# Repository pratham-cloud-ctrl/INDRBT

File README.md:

# INDRBT · Six-axis robot arm and parallel gripper

An original digital robotics project connecting mechanical design, robot mathematics, motion, feedback control and a routed KiCad interface board.

**[OPEN THE INTERACTIVE ENGINEERING SHOWCASE](https://pratham-cloud-ctrl.github.io/INDRBT/)** — inspect the 3D robot, 3D PCB, components, schematics and theory in your browser. No CAD application or GitHub sign-in is needed.

**[DOWNLOAD THE PUBLIC ENGINEERING PACKS](https://github.com/pratham-cloud-ctrl/INDRBT/releases/tag/indrbt-2026-10-28)** — STEP/STL CAD, native FreeCAD, the KiCad project, PCB STEP and a combined offline viewer/CAD pack. The repository and release are public; no private access is required. [Choose a format and open it](06_Complete_Project_Source/docs/cad_downloads.md). The published GitHub Pages showcase includes the browser viewers and download controls.

**[CAD & mechanical design](01_CAD_Models/README.md) · [Electronics & KiCad](04_Electronics/README.md) · [Theory & calculations](03_Reports_and_Results/README.md)**

**6 revolute joints · 54 CAD components · 790 mm nominal reach · 90 mm jaw opening**

Digital engineering model · v1.2.0 · DIGITAL SCOPE COMPLETE

## Explore the project on GitHub

You can inspect the design, drawings, circuit and calculations here without installing engineering software. Each tour starts with actual project images, then links to the native files and supporting evidence.

| Explore | Illustrated tour | Inspect the details |
|---|---|---|
| **Mechanical design** | [Arm, joints, tool interface and gripper](06_Complete_Project_Source/docs/cad_tour.md) | [Dimensioned drawings](01_CAD_Models/Drawings/engineering_interfaces.pdf) · [54-part catalog](06_Complete_Project_Source/docs/component_catalog.md) · [FreeCAD / STEP / STL](01_CAD_Models/README.md#download-and-edit) |
| **Electronics & KiCad** | [Follow power and signals through the board](06_Complete_Project_Source/docs/electronics_tour.md) | [Schematic PDF](04_Electronics/exports/joint_interface.pdf) · [PCB layers](04_Electronics/exports/pcb_layers.pdf) · [BOM](04_Electronics/bom.csv) · [Native KiCad project](04_Electronics/README.md#open-the-kicad-project) |
| **Theory & simulation** | [From geometry to a working digital task](06_Complete_Project_Source/docs/engineering_walkthrough.md) | [Equation guide](06_Complete_Project_Source/docs/theory_guide.md) · [Chapters and results](06_Complete_Project_Source/docs/README.md) · [Engineering report](06_Complete_Project_Source/docs/engineering_report.md) |

[Project purpose and original goals](06_Complete_Project_Source/docs/project_alignment.md) · [Complete documentation index](06_Complete_Project_Source/docs/README.md) · [Requirements and evidence](06_Complete_Project_Source/docs/validation_matrix.md)

## Watch the task, then inspect the design

The 9.24 s demonstration approaches, grasps, transfers and releases an object. The browser viewer animates the actual CAD meshes and can isolate every part. The GIF above is a forward-kinematics line view; object attachment is idealized in the simulation.

**Inspect online:** [move and isolate the robot](https://pratham-cloud-ctrl.github.io/INDRBT/#robot), [search the PCB and highlight nets](https://pratham-cloud-ctrl.github.io/INDRBT/#pcb), or [rotate the native 3D board](https://pratham-cloud-ctrl.github.io/INDRBT/#pcb3d). GitHub can decline previews of CAD files; the public showcase serves the actual display assets directly.

**For optional offline use:** [download the current repository](https://github.com/pratham-cloud-ctrl/INDRBT/archive/refs/heads/main.zip), extract it and open **OPEN_3D_VIEWER.cmd** on Windows. On any system, open `02_Simulation_and_Animation/Interactive_3D_Viewer.html` in a browser. It provides a local copy of the joint controls, part isolation and playback available online. GitHub shows this HTML source rather than executing it.

| Gripper and interchangeable tool interface | Routed joint / sensor interface |
|---|---|
|  |  |
| [Explore the mechanical design](06_Complete_Project_Source/docs/cad_tour.md) | [Explore the circuit and PCB](06_Complete_Project_Source/docs/electronics_tour.md) |

## Follow the engineering argument

The [engineering walkthrough](06_Complete_Project_Source/docs/engineering_walkthrough.md) follows one question: can the chosen geometry move a tool through a useful task, carry the assumed load in the analytical model, and track its commanded motion?

1. **Geometry → tool pose:** [Coordinate frames, FK, IK and the Jacobian](06_Complete_Project_Source/docs/02_kinematics.md).
2. **Pose → useful motion:** [Recorded task and motion limits](02_Simulation_and_Animation/README.md).
3. **Load → mechanical decisions:** [Gravity torque, drive sizing, stiffness and gripper calculations](06_Complete_Project_Source/docs/03_mechanical_analysis.md).
4. **Command → feedback:** [PID model and actual simulation curves](06_Complete_Project_Source/docs/theory_guide.md#8-understand-the-controller-experiment).
5. **Signals → interface hardware:** [Encoder, limit, external-drive and RS-485 circuit](06_Complete_Project_Source/docs/electronics_tour.md).

## What is verified

The [executed validation](06_Complete_Project_Source/results/validation/validation_report.md) records **91 tests with zero failures or errors**, native CAD inspection, sampled clearance, numerical checks and native KiCad ERC/DRC/connectivity checks. The [requirements matrix](06_Complete_Project_Source/docs/validation_matrix.md) maps each claim to its evidence; the [project journal](06_Complete_Project_Source/docs/project_journal.md) records actual faults and corrections.

Payload **4 kg** and repeatability **±0.1 mm** are targets. The project is entirely digital: analytical structure, simplified independent-axis control and sampled collision checks do not establish physical performance, manufacturing qualification, EMC or functional safety. The [scope audit](06_Complete_Project_Source/docs/digital_scope_audit.md) explains these boundaries.

## Find files or reproduce the work

| Folder | Start here |
|---|---|
| [01 · CAD models](01_CAD_Models/README.md) | Visual mechanical guide, native FreeCAD/Blender, six STEP/STL assemblies and 54 parts |
| [02 · Simulation and animation](02_Simulation_and_Animation/README.md) | Offline 3D viewer, recorded motion, workspace and PID plots |
| [03 · Theory, reports and results](03_Reports_and_Results/README.md) | Reading route, equations, calculations, experiments and verification |
| [04 · Electronics and KiCad](04_Electronics/README.md) | Schematic, board previews, native project, components and fabrication exports |
| [05 · Reference and project notes](05_Reference_and_Project_Notes/README.md) | Requirements, architecture, decisions and development journal |
| [06 · Complete source](06_Complete_Project_Source/README.md) | Installation, reproduction commands, scripts, tests and authoritative configuration |

After downloading, **OPEN_PROJECT_HOME.cmd** opens the local guide; **OPEN_FREECAD_MODEL.cmd** opens the solid assembly; **OPEN_PCB_LAYOUT.cmd** opens the board. Native CAD/KiCad files require their applications. PDF, PNG, SVG, CSV and Markdown provide immediate previews on GitHub.

The complete source is authoritative; numbered presentation folders contain verified copies. The [reproduction guide](06_Complete_Project_Source/README.md#run) and [contribution guide](CONTRIBUTING.md) explain regeneration. The last packaged engineering release is [v1.2.0](https://github.com/pratham-cloud-ctrl/INDRBT/releases/tag/indrbt-2026-10-28); the current repository includes the latest reading guides.

MIT-licensed original source · [License](LICENSE) · [Citation](CITATION.cff) · [Software checks](https://github.com/pratham-cloud-ctrl/INDRBT/actions/workflows/validation.yml)

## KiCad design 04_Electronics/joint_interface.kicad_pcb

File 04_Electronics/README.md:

# Electronics & KiCad · Joint / sensor interface

[← Project home](../README.md) · [CAD](../01_CAD_Models/README.md) · [Theory](../03_Reports_and_Results/README.md)

**[Inspect the interactive PCB](https://pratham-cloud-ctrl.github.io/INDRBT/#pcb) · [Rotate the 3D board](https://pratham-cloud-ctrl.github.io/INDRBT/#pcb3d) · [Zoom the schematic](https://pratham-cloud-ctrl.github.io/INDRBT/#schematic)**

Search components, cross-highlight the BOM, follow connected nets and inspect the actual board without installing KiCad.

**Start with the [illustrated circuit and PCB tour](../06_Complete_Project_Source/docs/electronics_tour.md).** Follow the regulated supply, encoder/limit inputs, external-drive commands and RS-485 interface, then match each block to the schematic and board.

**100 × 100 mm · Four copper layers · 44 schematic components · 48 PCB footprints including four mounting holes**

## Browse without KiCad

| Inspect | Open on GitHub |
|---|---|
| Circuit connections and values | [Schematic PDF](exports/joint_interface.pdf) · [Zoomable schematic SVG](exports/joint_interface.svg) |
| Board layout and references | [Top view](exports/pcb_top.png) · [Top copper SVG](exports/pcb_top.svg) · [Six-page layer PDF](exports/pcb_layers.pdf) |
| Ground, power and bottom routing | [Ground plane](exports/pcb_ground_plane.svg) · [Power plane](exports/pcb_power_plane.svg) · [Bottom copper](exports/pcb_bottom.svg) |
| Components and selection reasoning | [Component guide](../06_Complete_Project_Source/docs/electronics_components.md) · [BOM table](bom.csv) |
| Supply budget, filters and interface limits | [Electrical design chapter](../06_Complete_Project_Source/docs/05_electronics.md) · [Calculated values](interface_calculations.json) |
| Actual design-rule and connectivity evidence | [ERC](erc_report.json) · [DRC](pcb_drc_report.json) · [PCB verification](pcb_verification.json) |

References such as **U1**, **R5** or **J3** identify the same part in the schematic, layout and BOM. The tour explains the reference groups and **DNP** population choices.

## Open the KiCad project

**[Public KiCad and PCB STEP downloads](https://github.com/pratham-cloud-ctrl/INDRBT/releases/tag/indrbt-2026-10-28)** — the editable project with schematic, board and custom library context, plus board geometry for mechanical CAD. Follow the [opening guide](../06_Complete_Project_Source/docs/cad_downloads.md#open-the-kicad-project). GitHub downloads are public. The published GitHub Pages showcase includes the browser viewers and download controls.

1. For optional offline editing, download and extract the **complete repository**, keeping this folder together.
2. Open [joint_interface.kicad_pro](joint_interface.kicad_pro) in **KiCad 10**, then choose the schematic or PCB editor.
3. On Windows, **OPEN_PCB_LAYOUT.cmd** in the parent folder opens the routed board directly.

| Native item | File |
|---|---|
| KiCad project | [joint_interface.kicad_pro](joint_interface.kicad_pro) |
| Schematic | [joint_interface.kicad_sch](joint_interface.kicad_sch) |
| Routed PCB | [joint_interface.kicad_pcb](joint_interface.kicad_pcb) |
| Project-local library table | [fp-lib-table](fp-lib-table) |
| Manufacturer-specific fuse land pattern | [INDRBT_Interface.pretty](INDRBT_Interface.pretty) |

Keep the library table and local footprint folder beside the project. F1 uses a Bourns MF-NSMF025X-2 land pattern stored here; downloading only the PCB omits part of the editable project. The 3D render shows F1's lands because a dedicated fuse body model is not supplied.

## Fabrication and source

[Fabrication ZIP](fabrication/joint_interface_fabrication.zip) · [Gerbers, drills and positions](fabrication) · [Assembly drawing](exports/pcb_assembly.svg) · [Source and verification commands](../06_Complete_Project_Source/electronics/README.md)

This is a digital low-voltage interface for an external controller and drive. The board has no MCU or motor power stage. The E-stop connection monitors an auxiliary contact; it does not implement torque interruption. Native checks and fabrication exports are review evidence, with physical thermal, EMC and manufacturing qualification outside the project scope.

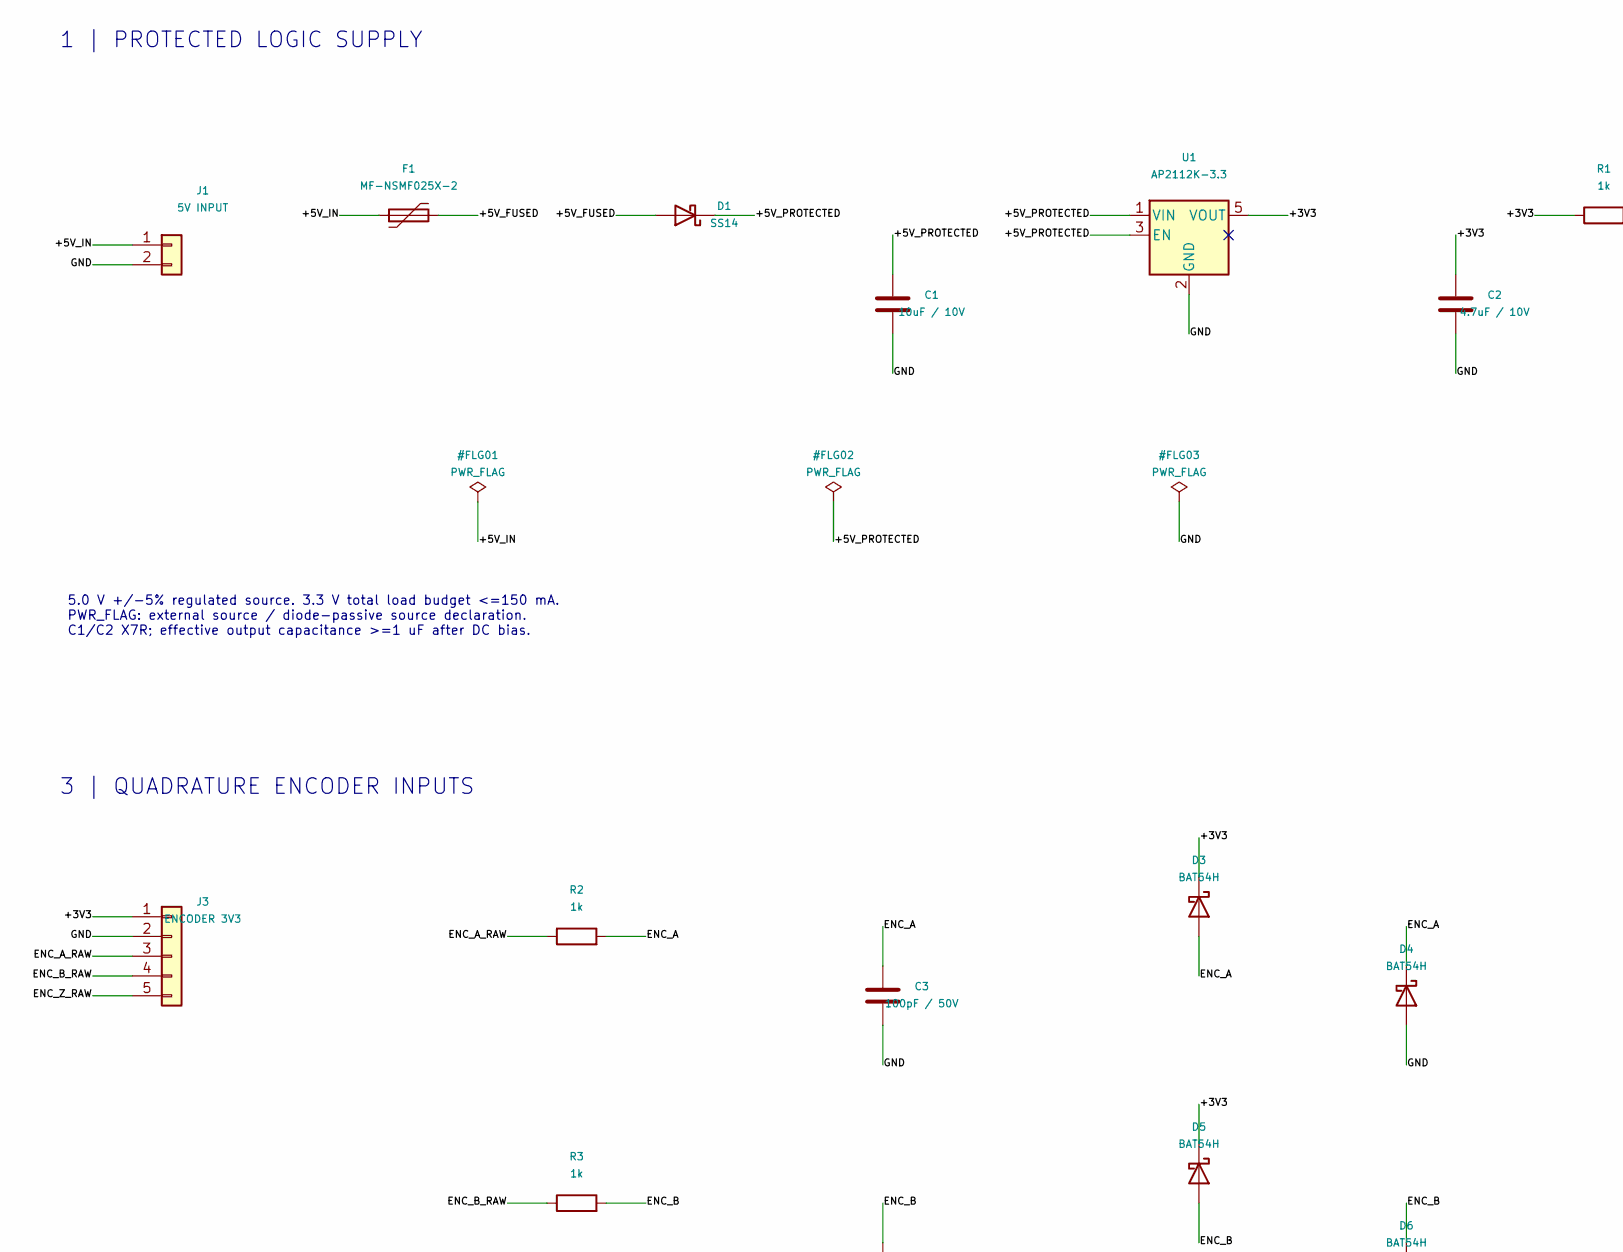
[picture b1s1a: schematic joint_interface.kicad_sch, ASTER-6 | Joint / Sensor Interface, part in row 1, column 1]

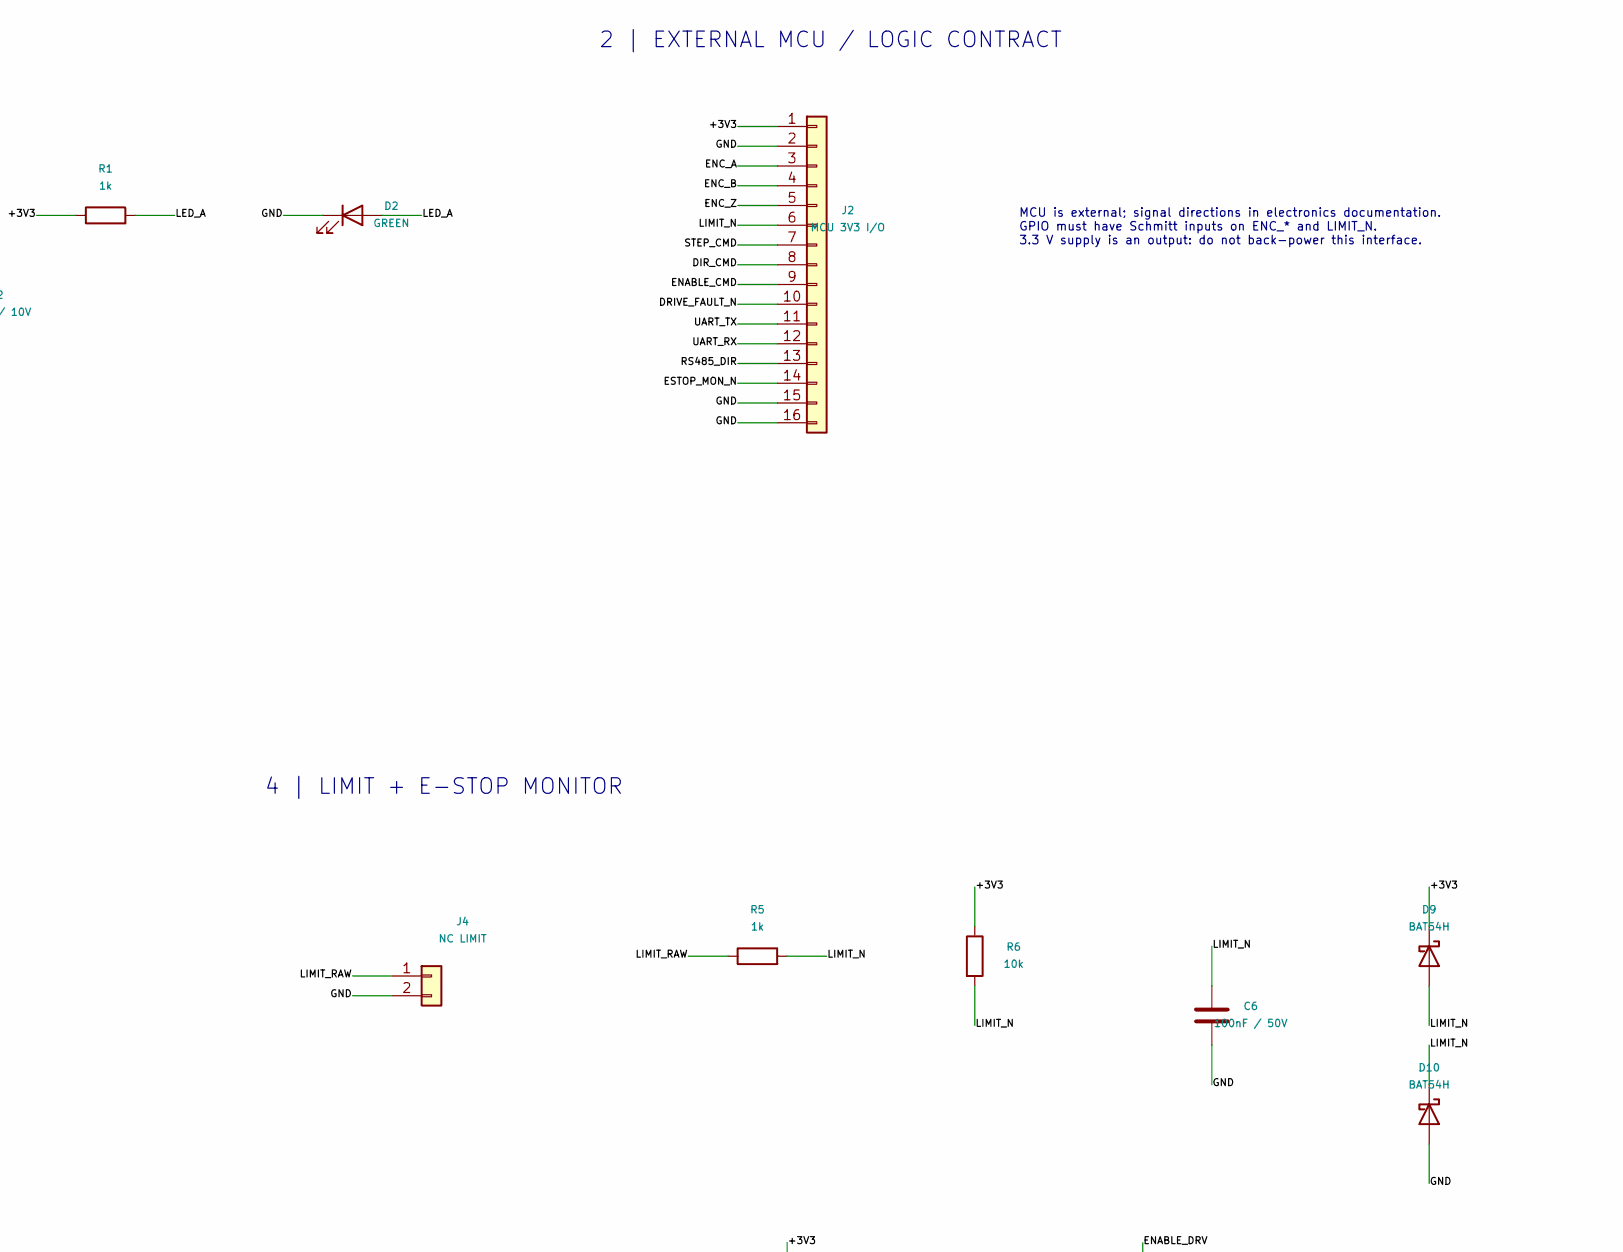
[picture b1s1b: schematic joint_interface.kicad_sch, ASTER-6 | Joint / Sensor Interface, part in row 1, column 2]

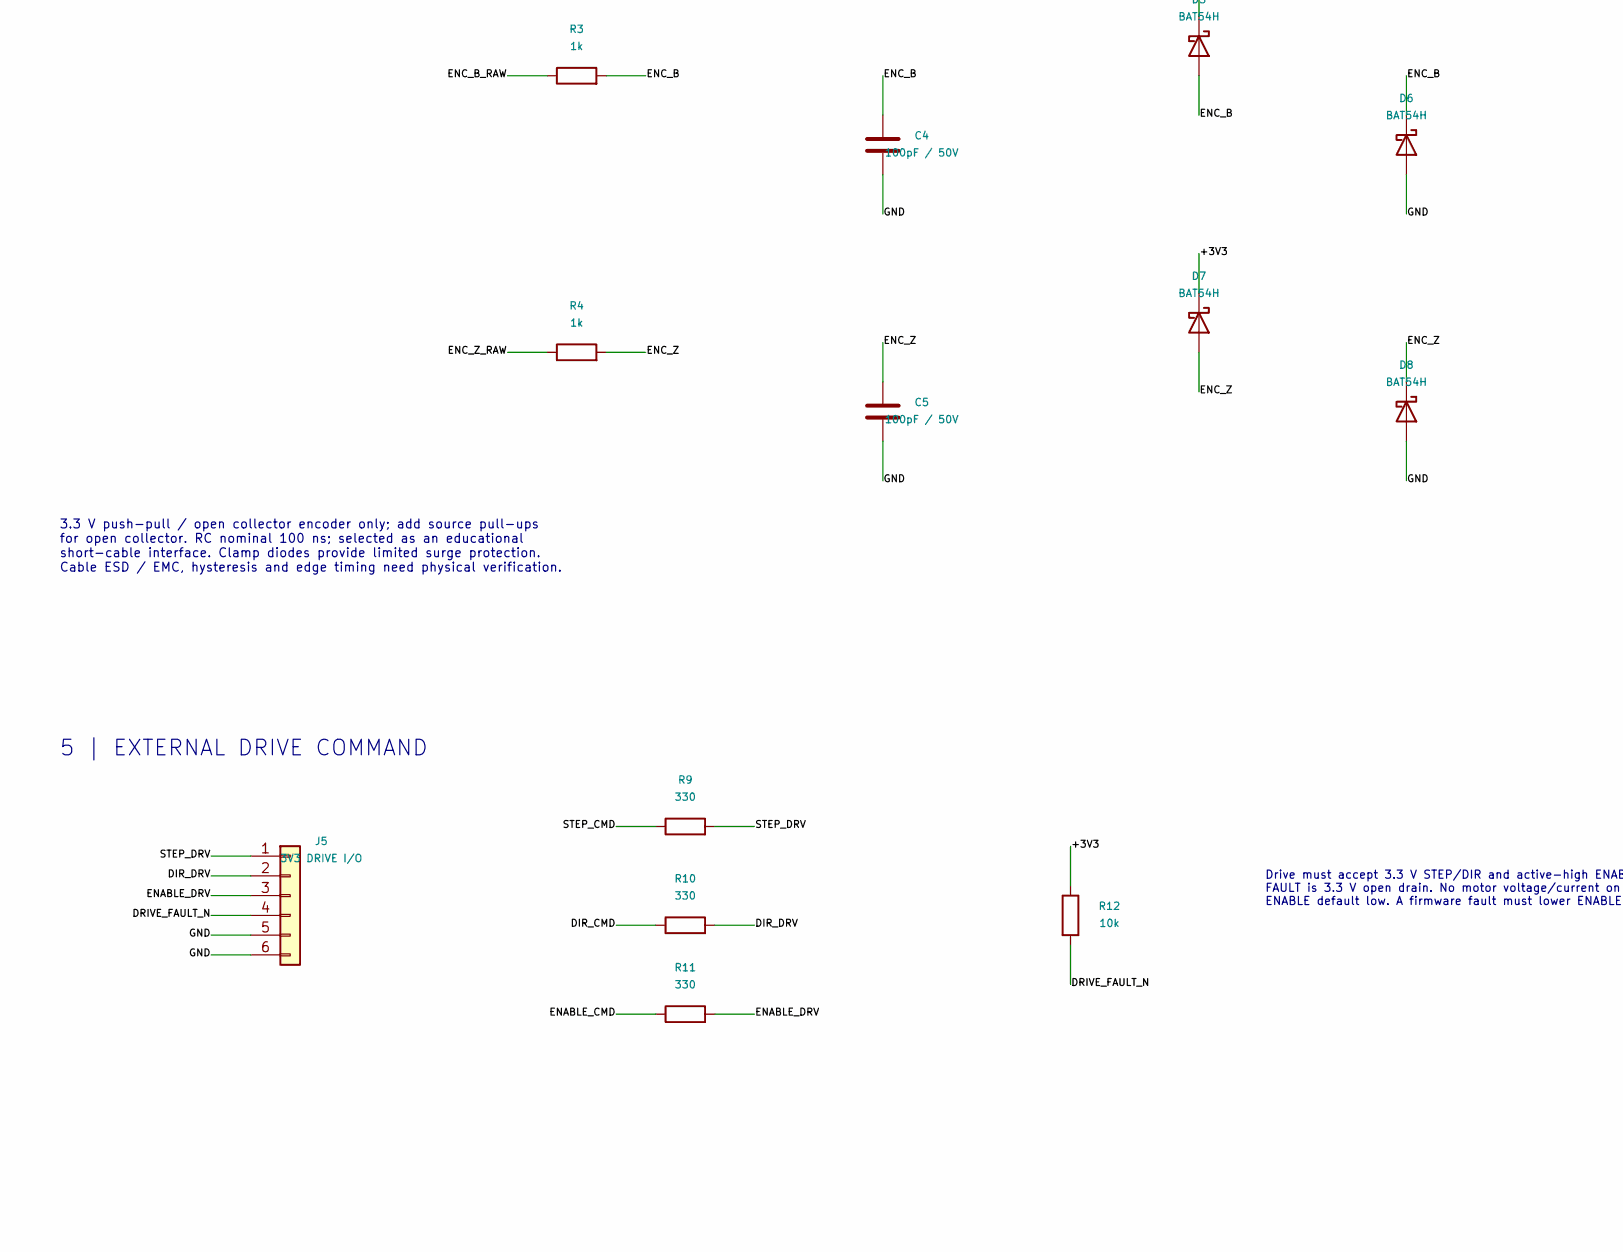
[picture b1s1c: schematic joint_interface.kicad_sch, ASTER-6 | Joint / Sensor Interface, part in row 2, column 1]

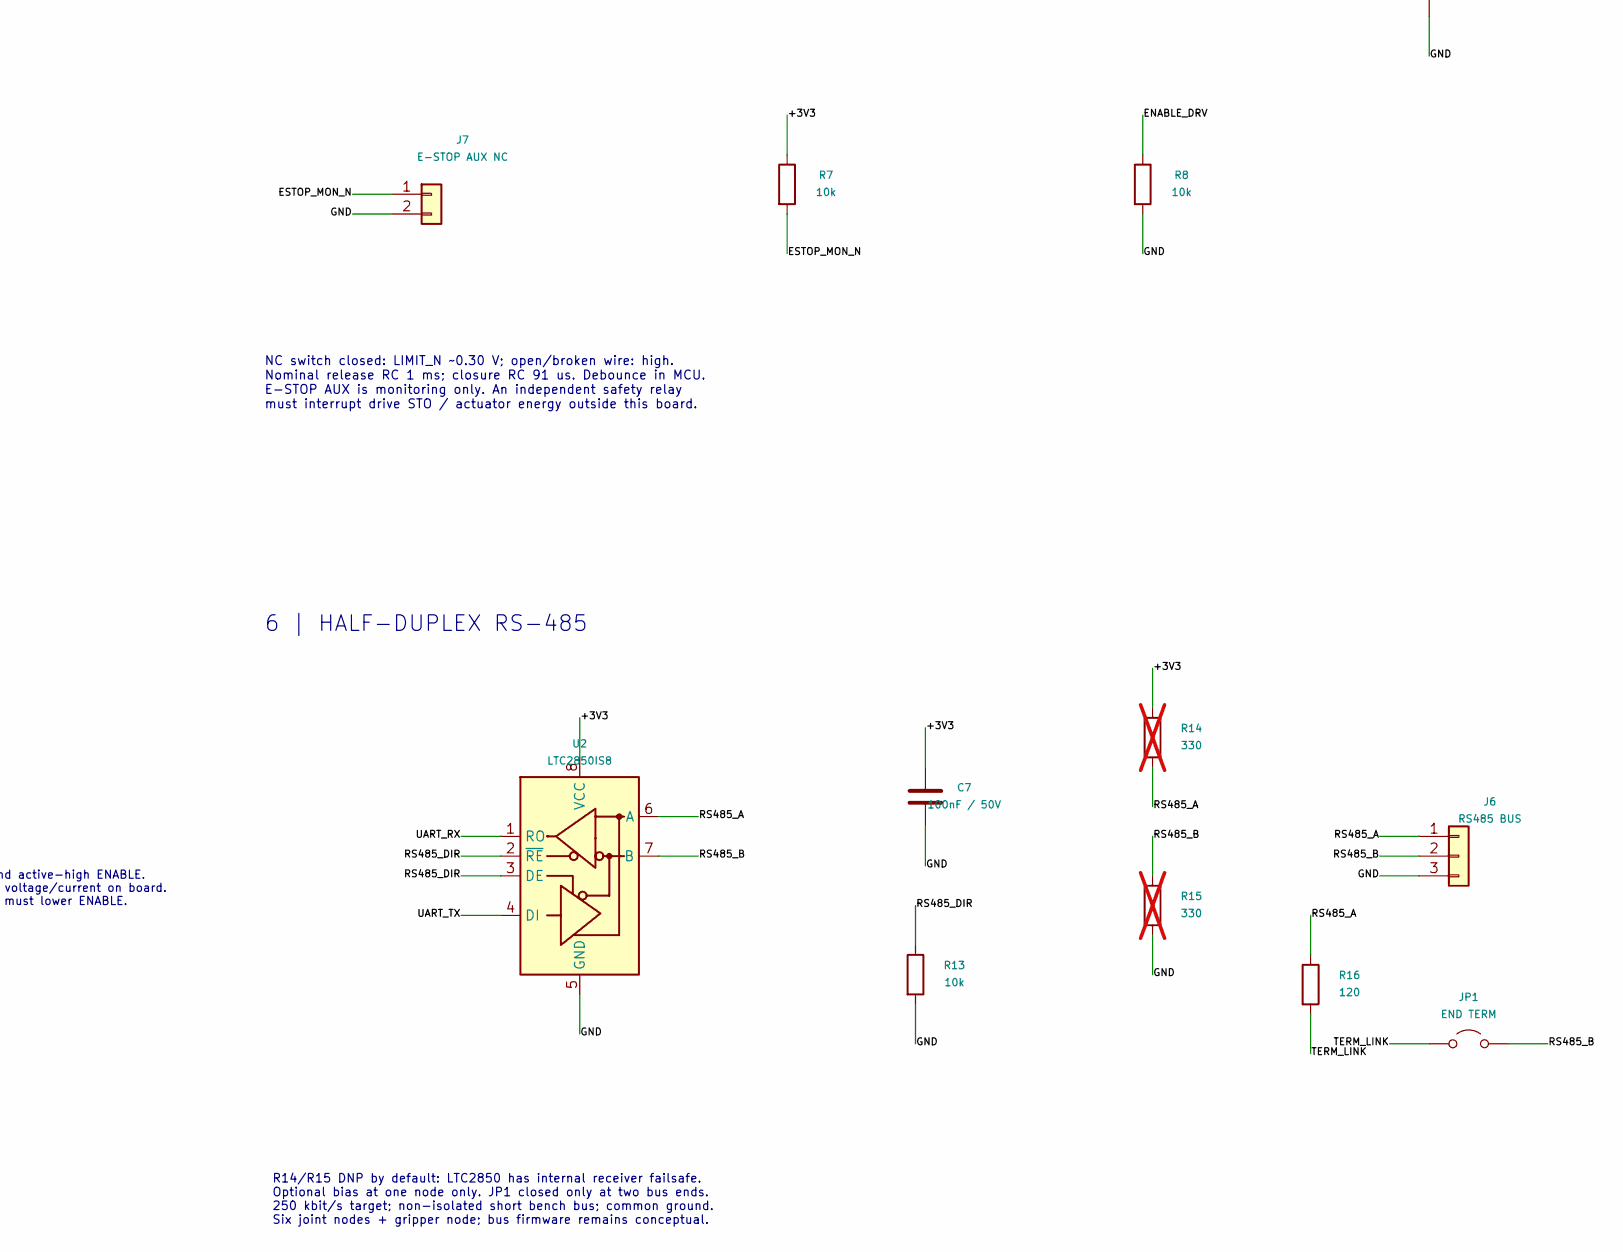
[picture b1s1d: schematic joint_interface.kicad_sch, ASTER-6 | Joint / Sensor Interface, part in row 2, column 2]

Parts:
C1: 10uF / 10V; C_0805_2012Metric
C2: 4.7uF / 10V; C_0805_2012Metric
C3, C4, C5: 100pF / 50V; C_0805_2012Metric
C6, C7: 100nF / 50V; C_0805_2012Metric
D1: SS14; D_SMA
D2: GREEN; LED_0805_2012Metric
D3, D4, D5, D6, D7, D8, D9, D10: BAT54H; D_SOD-123F
F1: MF-NSMF025X-2; PTC_Bourns_MF-NSMF025X_1206
J1: 5V INPUT; PinHeader_1x02_P2.54mm_Vertical
J2: MCU 3V3 I/O; PinHeader_1x16_P2.54mm_Vertical
J3: ENCODER 3V3; PinHeader_1x05_P2.54mm_Vertical
J4: NC LIMIT; PinHeader_1x02_P2.54mm_Vertical
J5: 3V3 DRIVE I/O; PinHeader_1x06_P2.54mm_Vertical
J6: RS485 BUS; PinHeader_1x03_P2.54mm_Vertical
J7: E-STOP AUX NC; PinHeader_1x02_P2.54mm_Vertical
JP1: END TERM; SolderJumper-2_P1.3mm_Open_Pad1.0x1.5mm
R1, R2, R3, R4, R5: 1k; R_0805_2012Metric
R6, R7, R8, R12, R13: 10k; R_0805_2012Metric
R9, R10, R11: 330; R_0805_2012Metric
R14, R15: 330; R_0805_2012Metric; not fitted
R16: 120; R_0805_2012Metric
U1: AP2112K-3.3; SOT-23-5
U2: LTC2850IS8; SOIC-8_3.9x4.9mm_P1.27mm

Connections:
/+3V3: C2.1, C7.1, D3.1 (K), D5.1 (K), D7.1 (K), D9.1 (K), J2.1, J3.1, R1.1, R6.1, R7.1, R12.1, R14.1, U1.5 (VOUT), U2.8 (VCC)
/+5V_FUSED: D1.2 (A), F1.2
/+5V_IN: F1.1, J1.1
/+5V_PROTECTED: C1.1, D1.1 (K), U1.1 (VIN), U1.3 (EN)
/DIR_CMD: J2.8, R10.1
/DIR_DRV: J5.2, R10.2
/DRIVE_FAULT_N: J2.10, J5.4, R12.2
/ENABLE_CMD: J2.9, R11.1
/ENABLE_DRV: J5.3, R8.1, R11.2
/ENC_A: C3.1, D3.2 (A), D4.1 (K), J2.3, R2.2
/ENC_A_RAW: J3.3, R2.1
/ENC_B: C4.1, D5.2 (A), D6.1 (K), J2.4, R3.2
/ENC_B_RAW: J3.4, R3.1
/ENC_Z: C5.1, D7.2 (A), D8.1 (K), J2.5, R4.2
/ENC_Z_RAW: J3.5, R4.1
/ESTOP_MON_N: J2.14, J7.1, R7.2
/GND: C1.2, C2.2, C3.2, C4.2, C5.2, C6.2, C7.2, D2.1 (K), D4.2 (A), D6.2 (A), D8.2 (A), D10.2 (A), J1.2, J2.2, J2.15, J2.16, J3.2, J4.2, J5.5, J5.6, J6.3, J7.2, R8.2, R13.2, R15.2, U1.2 (GND), U2.5 (GND)
/LED_A: D2.2 (A), R1.2
/LIMIT_N: C6.1, D9.2 (A), D10.1 (K), J2.6, R5.2, R6.2
/LIMIT_RAW: J4.1, R5.1
/RS485_A: J6.1, R14.2, R16.1, U2.6 (A)
/RS485_B: J6.2, JP1.2 (B), R15.1, U2.7 (B)
/RS485_DIR: J2.13, R13.1, U2.2 (~RE), U2.3 (DE)
/STEP_CMD: J2.7, R9.1
/STEP_DRV: J5.1, R9.2
/TERM_LINK: JP1.1 (A), R16.2
/UART_RX: J2.12, U2.1 (RO)
/UART_TX: J2.11, U2.4 (DI)

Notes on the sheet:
1 | PROTECTED LOGIC SUPPLY
5.0 V +/-5% regulated source. 3.3 V total load budget <=150 mA. PWR_FLAG: external source / diode-passive source declaration. C1/C2 X7R; effective output capacitance >=1 uF after DC bias.
2 | EXTERNAL MCU / LOGIC CONTRACT
MCU is external; signal directions in electronics documentation. GPIO must have Schmitt inputs on ENC_* and LIMIT_N. 3.3 V supply is an output: do not back-power this interface.
3 | QUADRATURE ENCODER INPUTS
3.3 V push-pull / open collector encoder only; add source pull-ups for open collector. RC nominal 100 ns; selected as an educational short-cable interface. Clamp diodes provide limited surge protection. Cable ESD / EMC, hysteresis and edge timing need physical verification.
4 | LIMIT + E-STOP MONITOR
NC switch closed: LIMIT_N ~0.30 V; open/broken wire: high. Nominal release RC 1 ms; closure RC 91 us. Debounce in MCU. E-STOP AUX is monitoring only. An independent safety relay must interrupt drive STO / actuator energy outside this board.
5 | EXTERNAL DRIVE COMMAND
Drive must accept 3.3 V STEP/DIR and active-high ENABLE. FAULT is 3.3 V open drain. No motor voltage/current on board. ENABLE default low. A firmware fault must lower ENABLE.
6 | HALF-DUPLEX RS-485
R14/R15 DNP by default: LTC2850 has internal receiver failsafe. Optional bias at one node only. JP1 closed only at two bus ends. 250 kbit/s target; non-isolated short bench bus; common ground. Six joint nodes + gripper node; bus firmware remains conceptual.

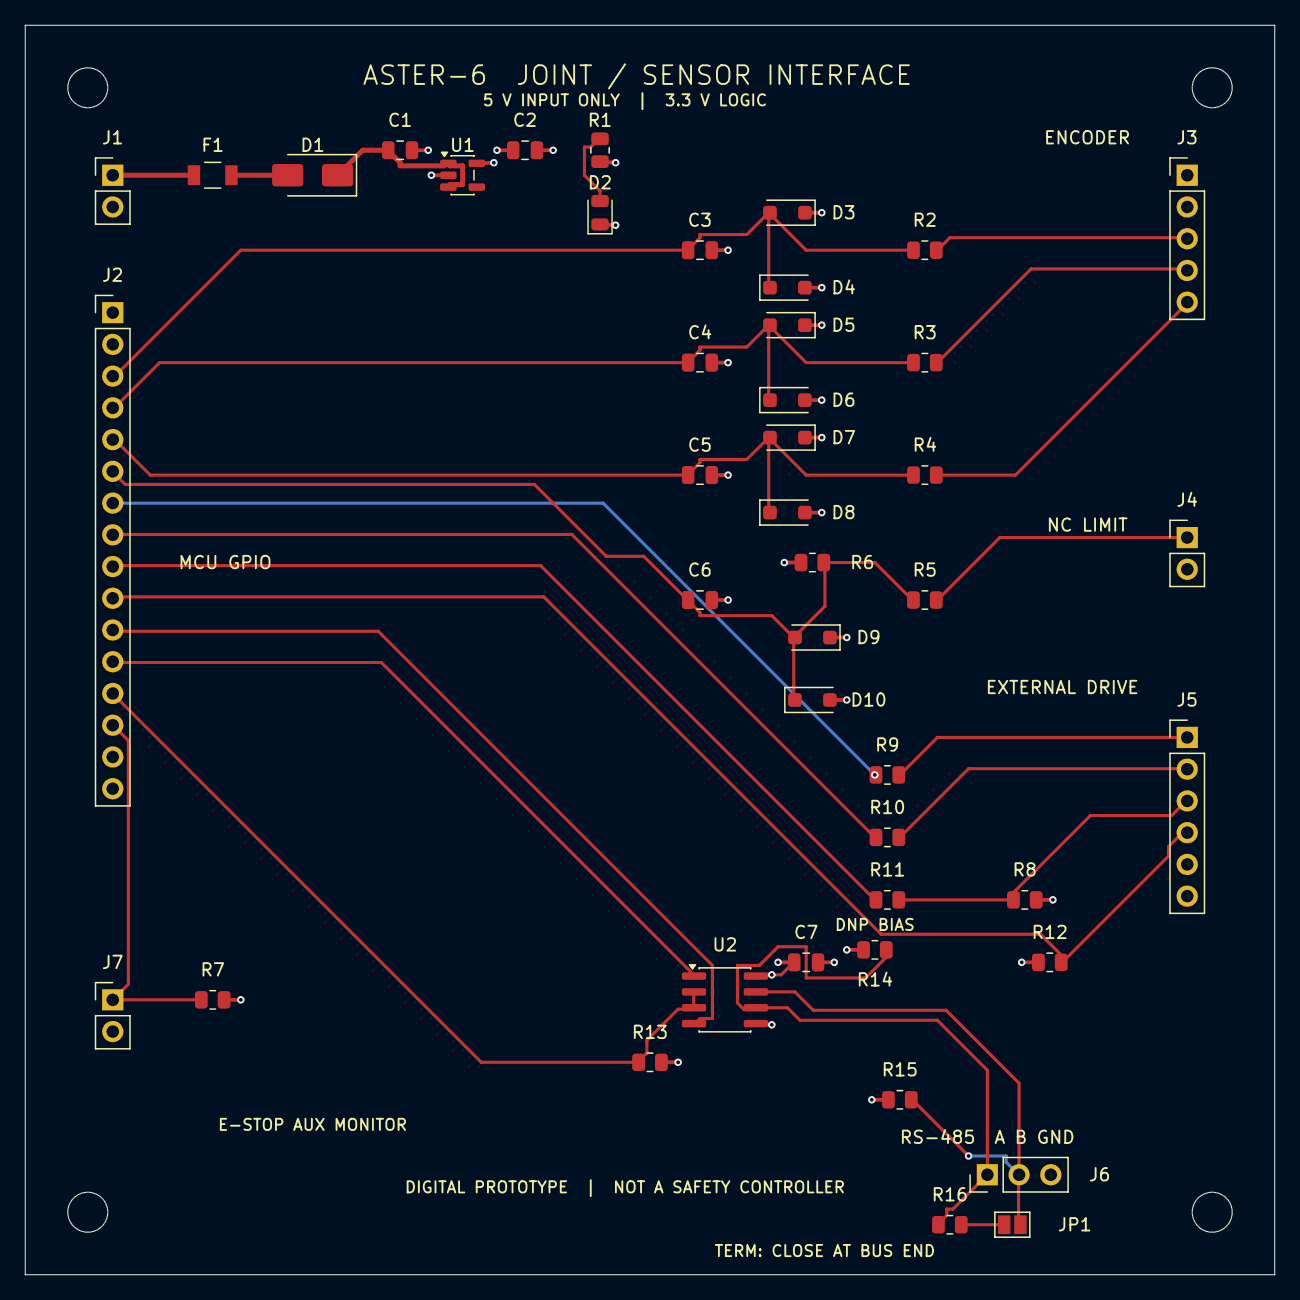
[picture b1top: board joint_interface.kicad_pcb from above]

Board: 4 copper layers, 100.0 x 100.0 mm, 48 parts (0 on the bottom side), 28 nets.

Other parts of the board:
H1, H2, H3, H4: M3 mounting; MountingHole_3.2mm_M3

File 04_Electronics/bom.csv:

Reference,Value,Footprint,Population,Description,Datasheet
J1,5V INPUT,Connector_PinHeader_2.54mm:PinHeader_1x02_P2.54mm_Vertical,Fit,"Generic connector, single row, 01x02, script generated (kicad-library-utils/schlib/autogen/connector/)",
F1,MF-NSMF025X-2,INDRBT_Interface:PTC_Bourns_MF-NSMF025X_1206,Fit,"Bourns PTC, 250 mA hold at 23 C; manufacturer nominal land pattern; trip/inrush unmeasured",https://www.bourns.com/docs/product-datasheets/mf-nsmf.pdf
D1,SS14,Diode_SMD:D_SMA,Fit,Schottky diode,https://www.vishay.com/docs/88746/ss12.pdf
C1,10uF / 10V,Capacitor_SMD:C_0805_2012Metric,Fit,Unpolarized capacitor,
U1,AP2112K-3.3,Package_TO_SOT_SMD:SOT-23-5,Fit,"600mA low dropout linear regulator, with enable pin, 3.8V-6V input voltage range, 3.3V fixed positive output, SOT-23-5",https://www.diodes.com/assets/Datasheets/AP2112.pdf
C2,4.7uF / 10V,Capacitor_SMD:C_0805_2012Metric,Fit,Unpolarized capacitor,
R1,1k,Resistor_SMD:R_0805_2012Metric,Fit,Resistor,
D2,GREEN,LED_SMD:LED_0805_2012Metric,Fit,3.3 V rail status indicator,
J2,MCU 3V3 I/O,Connector_PinHeader_2.54mm:PinHeader_1x16_P2.54mm_Vertical,Fit,"Generic connector, single row, 01x16, script generated (kicad-library-utils/schlib/autogen/connector/)",
J3,ENCODER 3V3,Connector_PinHeader_2.54mm:PinHeader_1x05_P2.54mm_Vertical,Fit,"Generic connector, single row, 01x05, script generated (kicad-library-utils/schlib/autogen/connector/)",
R2,1k,Resistor_SMD:R_0805_2012Metric,Fit,Resistor,
C3,100pF / 50V,Capacitor_SMD:C_0805_2012Metric,Fit,Unpolarized capacitor,
D3,BAT54H,Diode_SMD:D_SOD-123F,Fit,Schottky diode,https://assets.nexperia.com/documents/data-sheet/BAT54H.pdf
D4,BAT54H,Diode_SMD:D_SOD-123F,Fit,Schottky diode,https://assets.nexperia.com/documents/data-sheet/BAT54H.pdf
R3,1k,Resistor_SMD:R_0805_2012Metric,Fit,Resistor,
C4,100pF / 50V,Capacitor_SMD:C_0805_2012Metric,Fit,Unpolarized capacitor,
D5,BAT54H,Diode_SMD:D_SOD-123F,Fit,Schottky diode,https://assets.nexperia.com/documents/data-sheet/BAT54H.pdf
D6,BAT54H,Diode_SMD:D_SOD-123F,Fit,Schottky diode,https://assets.nexperia.com/documents/data-sheet/BAT54H.pdf
R4,1k,Resistor_SMD:R_0805_2012Metric,Fit,Resistor,
C5,100pF / 50V,Capacitor_SMD:C_0805_2012Metric,Fit,Unpolarized capacitor,
D7,BAT54H,Diode_SMD:D_SOD-123F,Fit,Schottky diode,https://assets.nexperia.com/documents/data-sheet/BAT54H.pdf
D8,BAT54H,Diode_SMD:D_SOD-123F,Fit,Schottky diode,https://assets.nexperia.com/documents/data-sheet/BAT54H.pdf
J4,NC LIMIT,Connector_PinHeader_2.54mm:PinHeader_1x02_P2.54mm_Vertical,Fit,"Generic connector, single row, 01x02, script generated (kicad-library-utils/schlib/autogen/connector/)",
R5,1k,Resistor_SMD:R_0805_2012Metric,Fit,Resistor,
R6,10k,Resistor_SMD:R_0805_2012Metric,Fit,Resistor,
C6,100nF / 50V,Capacitor_SMD:C_0805_2012Metric,Fit,Unpolarized capacitor,
D9,BAT54H,Diode_SMD:D_SOD-123F,Fit,Schottky diode,https://assets.nexperia.com/documents/data-sheet/BAT54H.pdf
D10,BAT54H,Diode_SMD:D_SOD-123F,Fit,Schottky diode,https://assets.nexperia.com/documents/data-sheet/BAT54H.pdf
J7,E-STOP AUX NC,Connector_PinHeader_2.54mm:PinHeader_1x02_P2.54mm_Vertical,Fit,"Generic connector, single row, 01x02, script generated (kicad-library-utils/schlib/autogen/connector/)",
R7,10k,Resistor_SMD:R_0805_2012Metric,Fit,Resistor,
R8,10k,Resistor_SMD:R_0805_2012Metric,Fit,Resistor,
J5,3V3 DRIVE I/O,Connector_PinHeader_2.54mm:PinHeader_1x06_P2.54mm_Vertical,Fit,"Generic connector, single row, 01x06, script generated (kicad-library-utils/schlib/autogen/connector/)",
R9,330,Resistor_SMD:R_0805_2012Metric,Fit,Resistor,
R10,330,Resistor_SMD:R_0805_2012Metric,Fit,Resistor,
R11,330,Resistor_SMD:R_0805_2012Metric,Fit,Resistor,
R12,10k,Resistor_SMD:R_0805_2012Metric,Fit,Resistor,
U2,LTC2850IS8,Package_SO:SOIC-8_3.9x4.9mm_P1.27mm,Fit,"RS-485, RS-422 Half-duplex 20Mbps transceiver, SOIC-8",https://www.analog.com/media/en/technical-documentation/data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
C7,100nF / 50V,Capacitor_SMD:C_0805_2012Metric,Fit,Unpolarized capacitor,
R13,10k,Resistor_SMD:R_0805_2012Metric,Fit,Resistor,
J6,RS485 BUS,Connector_PinHeader_2.54mm:PinHeader_1x03_P2.54mm_Vertical,Fit,"Generic connector, single row, 01x03, script generated (kicad-library-utils/schlib/autogen/connector/)",
R14,330,Resistor_SMD:R_0805_2012Metric,DNP by default,Resistor,
R15,330,Resistor_SMD:R_0805_2012Metric,DNP by default,Resistor,
R16,120,Resistor_SMD:R_0805_2012Metric,Fit,Resistor,
JP1,END TERM,Jumper:SolderJumper-2_P1.3mm_Open_Pad1.0x1.5mm,Fit,"Jumper, 2-pole, open",
